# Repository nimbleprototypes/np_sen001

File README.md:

np_sen001
=========

Sensor de temperatura MCP9700

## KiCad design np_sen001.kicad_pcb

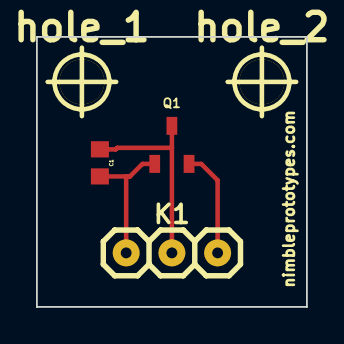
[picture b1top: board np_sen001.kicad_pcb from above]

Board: 2 copper layers, 15.0 x 15.0 mm, 5 parts (0 on the bottom side), 3 nets.

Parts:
C1: C; CAP-0603
K1: HEADER_3; HEADER-3
Q1: MCP9700; SOT-3
hole_1, hole_2: hole_2mm5

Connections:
unnamed: K1.3, Q1.2
unnamed: C1.2, K1.2, Q1.3
unnamed: C1.1, K1.1, Q1.1
